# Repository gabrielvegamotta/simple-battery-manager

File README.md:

# Simple Battery Manager
A low cost simple battery manager breakout board. You can use it with any MCU for battery monitoring! 

This board is designed for efficiently monitoring battery voltage without causing any significant current drain on the battery itself. Also have the feature of auto-switch between VBAT and a 5V input, so you don't need to unplug the battery when conecting a USB power supply for example.

You can change the voltage divider (R2 and R3) to match your voltages and measurement needs.

JP1 is for current measurement.

### Documentation

- [Schematic](https://github.com/gabrielvegamotta/simple-battery-manager/blob/main/pdfs/SCH-simple-battery-manager-v1.pdf)
- [Layout](https://github.com/gabrielvegamotta/simple-battery-manager/blob/main/pdfs/PCB-simple-battery-manager-v1.pdf)
- [BOM](https://github.com/gabrielvegamotta/simple-battery-manager/blob/main/bom/ibom.html)

### PCB Assembled

More info soon.

### Performance & Results

More info soon.

### Final Thoughts

More info soon.

### References
 - [Battery-Voltage-Measure by hallard](https://github.com/hallard/Battery-Voltage-Measure)
 - [Nordic Thingy Battery Monitoring, Page 65](https://infocenter.nordicsemi.com/pdf/Thingy_UG_v1.0.pdf)

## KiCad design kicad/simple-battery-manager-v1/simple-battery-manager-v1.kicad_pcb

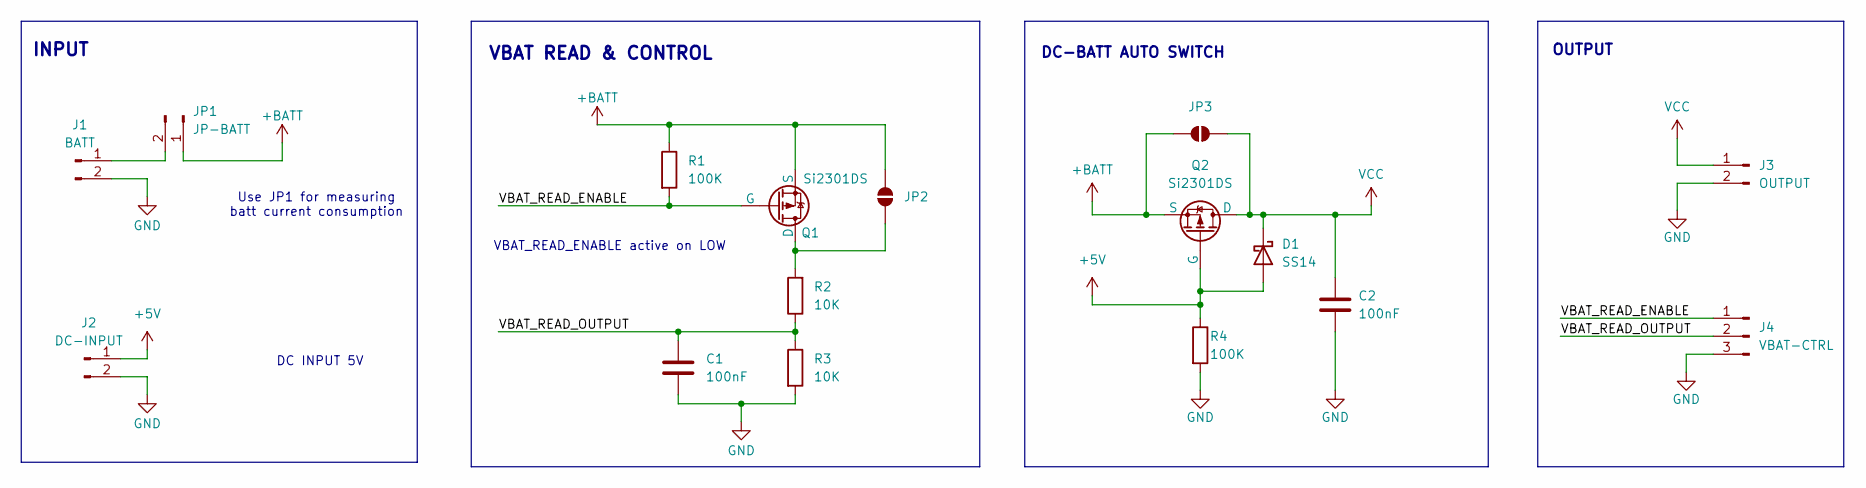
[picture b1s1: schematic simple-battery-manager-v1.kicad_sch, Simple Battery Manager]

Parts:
C1, C2: 100nF; C_0603_1608Metric_Pad1.08x0.95mm_HandSolder
D1: SS14; D_SMA
J1: BATT; PinHeader_1x02_P2.54mm_Vertical
J2: DC-INPUT; PinHeader_1x02_P2.54mm_Vertical
J3: OUTPUT; PinHeader_1x02_P2.54mm_Vertical
J4: VBAT-CTRL; PinHeader_1x03_P2.54mm_Vertical
JP1: JP-BATT; PinHeader_1x02_P2.54mm_Vertical
JP2, JP3: SolderJumper_2_Open; SolderJumper-2_P1.3mm_Open_TrianglePad1.0x1.5mm
Q1, Q2: Si2301DS; SOT-23_Handsoldering
R1, R4: 100K; R_0603_1608Metric_Pad0.98x0.95mm_HandSolder
R2, R3: 10K; R_0603_1608Metric_Pad0.98x0.95mm_HandSolder

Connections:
+5V: D1.2 (A), J2.1, Q2.2 (G), R4.1
+BATT: JP1.1, JP2.2 (B), JP3.2 (B), Q1.3 (S), Q2.3 (S), R1.1
/VBAT_READ_ENABLE: J4.1, Q1.2 (G), R1.2
/VBAT_READ_OUTPUT: C1.2, J4.2, R2.1, R3.1
GND: C1.1, C2.2, J1.2, J2.2, J3.2, J4.3, R3.2, R4.2
unnamed: J1.1, JP1.2
unnamed: JP2.1 (A), Q1.1 (D), R2.2
VCC: C2.1, D1.1 (K), J3.1, JP3.1 (A), Q2.1 (D)

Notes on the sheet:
VBAT_READ_ENABLE active on LOW
OUTPUT
DC INPUT 5V
DC-BATT AUTO SWITCH
INPUT
VBAT READ & CONTROL
Use JP1 for measuring batt current consumption

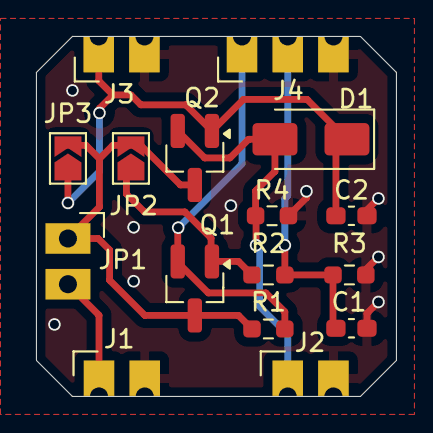
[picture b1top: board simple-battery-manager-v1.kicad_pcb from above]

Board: 2 copper layers, 20.0 x 20.0 mm, 16 parts (0 on the bottom side), 8 nets.

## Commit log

2024-04-03 Project created. Add template sheet. Add input, vbat read control, dc-batt autoswitch and ouput circuits.
2024-04-03 Add dru pcb for jlcpcb
2024-04-03 Add datasheet si2301
2024-04-07 Updated autoswitch circuit, added D1. Added Headers for Vbat read and enable
2024-04-07 Initial layout of components. Pcb 25x25mm
2024-04-08 Update footprints to 0603
2024-04-08 Layout and routing
2024-04-16 Sch finished.
2024-04-16 Created pdf sch
2024-04-16 pcb finished
2024-04-16 Update title block.
2024-04-16 Created pdf pcb
2024-04-16 Created gerber files from gerber to order
2024-04-27 Created iBOM
